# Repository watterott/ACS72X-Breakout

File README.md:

# ACS72X-Breakout
Breakout with AllegroMicro ACS724 or ACS725 Hall-Effect Current Sensor.

* AllegroMicro [ACS724 5V](https://www.allegromicro.com/en/Products/Current-Sensor-ICs/Zero-To-Fifty-Amp-Integrated-Conductor-Sensor-ICs/ACS724.aspx) or [ACS725 3.3V](https://www.allegromicro.com/en/Products/Current-Sensor-ICs/Zero-To-Fifty-Amp-Integrated-Conductor-Sensor-ICs/ACS725.aspx) Hall-Effect Current Sensor
* Differential Hall sensing rejects common-mode fields
* Integrated digital temperature compensation circuitry allows for near closed loop accuracy over temperature in an open-loop sensor
* Output voltage proportional to AC or DC current
* Open-Source and released under the [Creative Commons Attribution Share-Alike License](https://creativecommons.org/licenses/by-sa/4.0/).
* **[Documentation on learn.watterott.com](https://learn.watterott.com)**

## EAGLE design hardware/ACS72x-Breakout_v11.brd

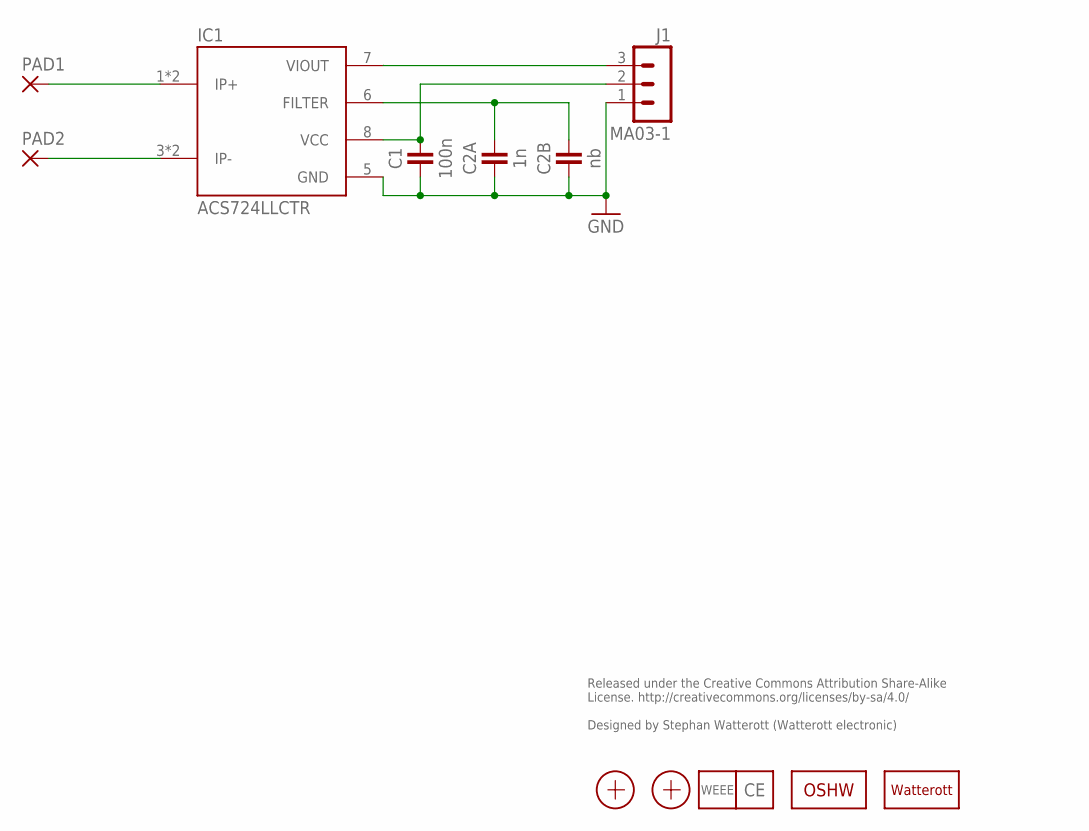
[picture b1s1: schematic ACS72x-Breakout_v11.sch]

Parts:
C1: 100n; C0402
C2A: 1n; C0402
C2B: nb; C0603
IC1: ACS724LLCTR; SO8
J1: MA03-1
LOGO1: LOGO_CE-2; CE_2MM
LOGO2: OSHW_LOGOX0070; OSHW_6X70
LOGO3: LOGO-S_PLACE_S; SPARK_TPLACE_S
LOGO4: LOGO_WEEE-4; WEEE_4MM
PAD1, PAD2: WIREPADSMD5-2,5; 5-2,5
X1, X2: PASSER-07; PASSER_07MM

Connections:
FLT: C2A.2, C2B.2, IC1.6 (FILTER)
GND: C1.1, C2A.1, C2B.1, IC1.5 (GND), J1.1
IP+: IC1.1 (IP+), IC1.2 (IP+), PAD1.1
IP-: IC1.3 (IP-), IC1.4 (IP-), PAD2.1
VCC: C1.2, IC1.8 (VCC), J1.2
VIOUT: IC1.7 (VIOUT), J1.3

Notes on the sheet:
Released under the Creative Commons Attribution Share-Alike License. http://creativecommons.org/licenses/by-sa/4.0/ Designed by Stephan Watterott (Watterott electronic)

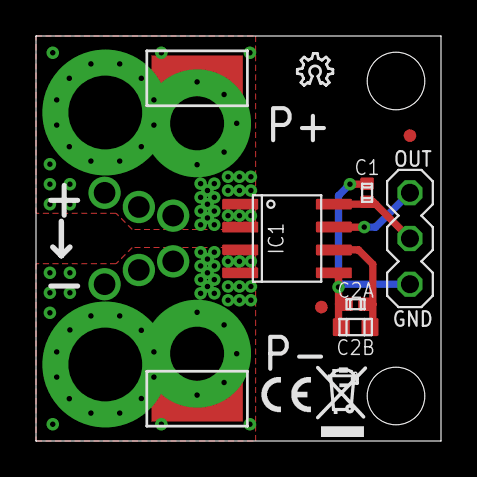
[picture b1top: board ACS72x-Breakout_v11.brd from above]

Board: 2 copper layers, 22.5 x 22.5 mm, 13 parts (1 on the bottom side), 6 nets.

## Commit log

2020-10-07 Add files via upload
    added V11
